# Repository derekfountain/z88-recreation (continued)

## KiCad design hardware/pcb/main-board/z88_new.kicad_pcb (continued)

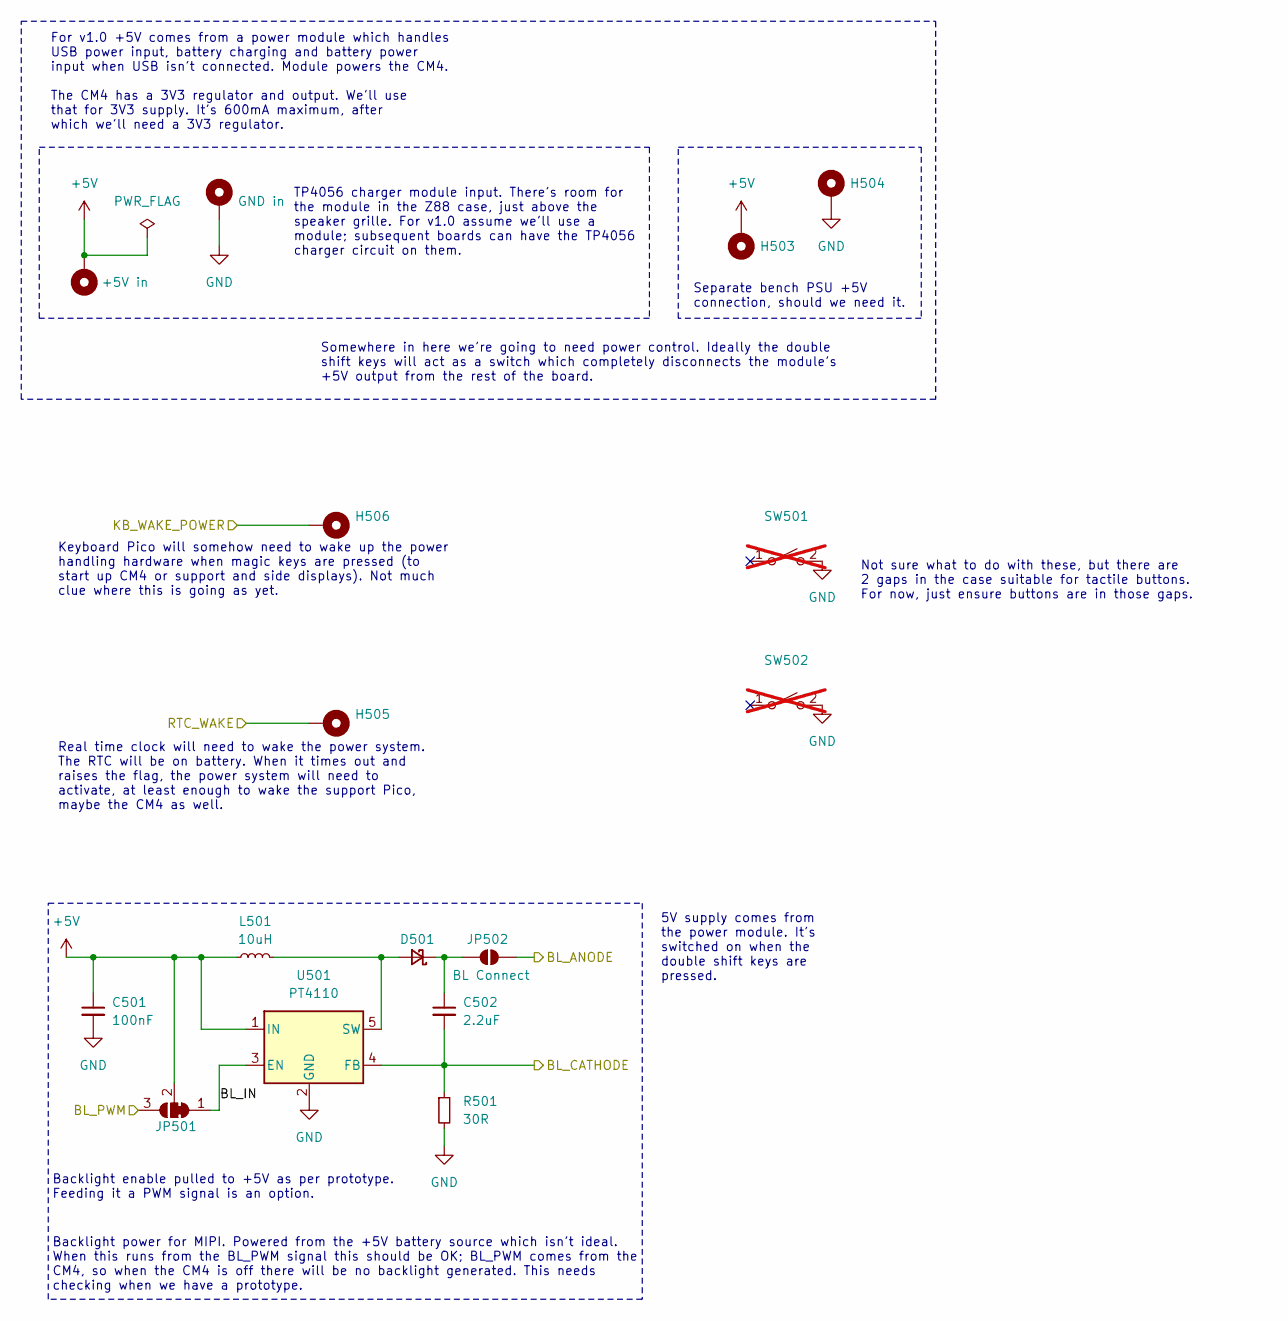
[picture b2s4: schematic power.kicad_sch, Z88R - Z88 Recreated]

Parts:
C501: 100nF; C_0805_2012Metric_Pad1.18x1.45mm_HandSolder
C502: 2.2uF; C_0805_2012Metric_Pad1.18x1.45mm_HandSolder
D501: D_Schottky_Small; D_1206_3216Metric_Pad1.42x1.75mm_HandSolder
H501: +5V in; MountingHole_2.2mm_M2_Pad
H502: GND in; MountingHole_2.2mm_M2_Pad
H503: +5V; MountingHole_2.2mm_M2_Pad
H504: GND; MountingHole_2.2mm_M2_Pad
H505: RTC Wake; TestPoint_THTPad_D2.0mm_Drill1.0mm
H506: KB Wake Power; TestPoint_THTPad_D2.0mm_Drill1.0mm
JP501: BL Source; SolderJumper-3_P1.3mm_Bridged2Bar12_Pad1.0x1.5mm
JP502: BL Connect; SolderJumper-2_P1.3mm_Open_Pad1.0x1.5mm
L501: 10uH; L_Coilcraft_XAL7070-XXX
R501: 30R; R_0805_2012Metric_Pad1.20x1.40mm_HandSolder
SW501, SW502: NO POP; SW_Tactile_SKHH_Angled; not fitted
U501: PT4110; SOT-89-5_Handsoldering

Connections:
+5V: C501.1, H501.1, H503.1, JP501.2 (C), L501.1, U501.1 (IN); also elsewhere on the board
/CM4_GPIO/BL_PWM: JP501.3 (B); also elsewhere on the board
/CM4_HighSpeed/BL_ANODE: JP502.2 (B); also elsewhere on the board
/CM4_HighSpeed/BL_CATHODE: C502.2, R501.1, U501.4 (FB); also elsewhere on the board
/Keyboard/KB_WAKE_POWER: H506.1; also elsewhere on the board
/Power/BL_IN: JP501.1 (A), U501.3 (EN)
/Power/RTC_WAKE: H505.1; also elsewhere on the board
GND: C501.2, H502.1, H504.1, R501.2, SW501.2 (B), SW502.2 (B), U501.2 (GND); also elsewhere on the board
unnamed: D501.2 (A), L501.2, U501.5 (SW)
unnamed: C502.1, D501.1 (K), JP502.1 (A)

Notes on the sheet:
Somewhere in here we're going to need power control. Ideally the double shift keys will act as a switch which completely disconnects the module's +5V output from the rest of the board.
For v1.0 +5V comes from a power module which handles USB power input, battery charging and battery power input when USB isn't connected. Module powers the CM4. The CM4 has a 3V3 regulator and output. We'll use that for 3V3 supply. It's 600mA maximum, after which we'll need a 3V3 regulator.
TP4056 charger module input. There's room for the module in the Z88 case, just above the speaker grille. For v1.0 assume we'll use a module; subsequent boards can have the TP4056 charger circuit on them.
Backlight power for MIPI. Powered from the +5V battery source which isn't ideal. When this runs from the BL_PWM signal this should be OK; BL_PWM comes from the CM4, so when the CM4 is off there will be no backlight generated. This needs checking when we have a prototype.
Real time clock will need to wake the power system. The RTC will be on battery. When it times out and raises the flag, the power system will need to activate, at least enough to wake the support Pico, maybe the CM4 as well.
Keyboard Pico will somehow need to wake up the power handling hardware when magic keys are pressed (to start up CM4 or support and side displays). Not much clue where this is going as yet.
Separate bench PSU +5V connection, should we need it.
Backlight enable pulled to +5V as per prototype. Feeding it a PWM signal is an option.
Not sure what to do with these, but there are 2 gaps in the case suitable for tactile buttons. For now, just ensure buttons are in those gaps.
5V supply comes from the power module. It's switched on when the double shift keys are pressed.

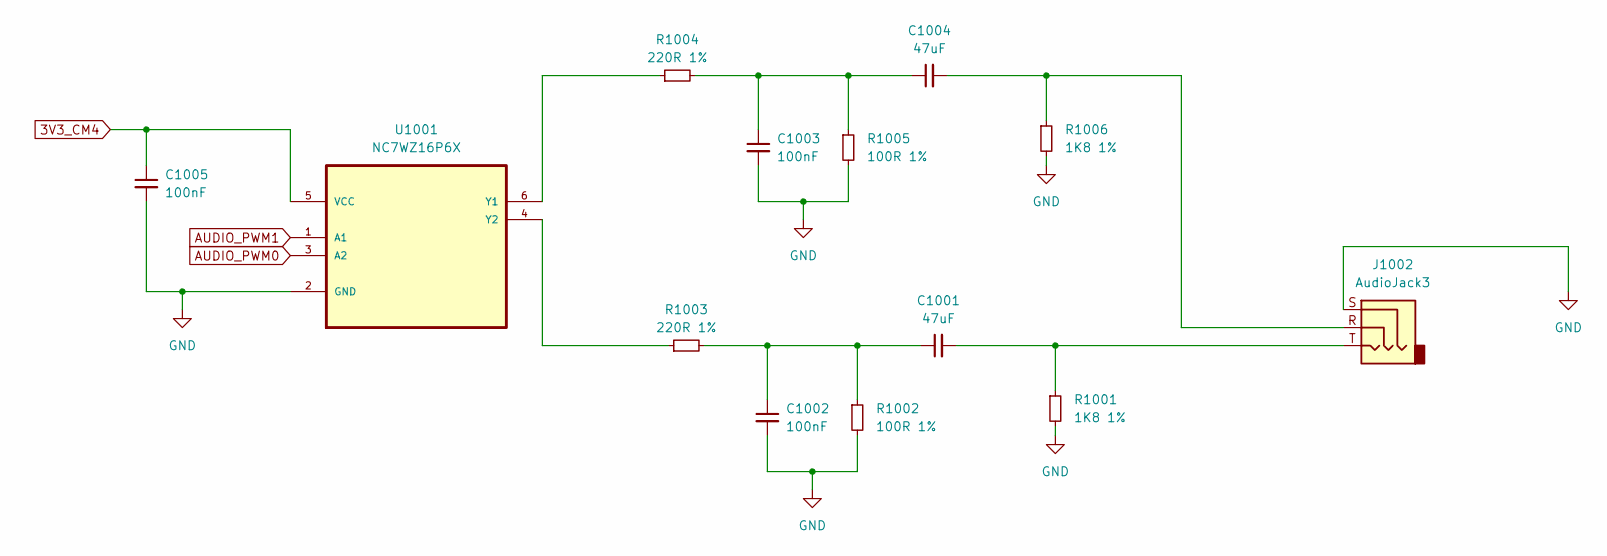
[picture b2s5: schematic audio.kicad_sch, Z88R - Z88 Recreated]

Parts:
C1001, C1004: 47uF; C_0805_2012Metric_Pad1.18x1.45mm_HandSolder
C1002, C1003, C1005: 100nF; C_0805_2012Metric_Pad1.18x1.45mm_HandSolder
J1002: AudioJack3; Jack_3.5mm_CUI_SJ1-3533NG_Horizontal
R1001, R1006: 1K8 1%; R_0805_2012Metric_Pad1.20x1.40mm_HandSolder
R1002, R1005: 100R 1%; R_0805_2012Metric_Pad1.20x1.40mm_HandSolder
R1003, R1004: 220R 1%; R_0805_2012Metric_Pad1.20x1.40mm_HandSolder
U1001: NC7WZ16P6X; SOT-363_SC-70-6_Handsoldering; MPN NC7WZ16P6X

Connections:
3V3_CM4: C1005.1, U1001.5 (VCC); also elsewhere on the board
AUDIO_PWM0: U1001.3 (A2); also elsewhere on the board
AUDIO_PWM1: U1001.1 (A1); also elsewhere on the board
GND: C1002.2, C1003.2, C1005.2, J1002.S, R1001.2, R1002.2, R1005.2, R1006.2, U1001.2 (GND); also elsewhere on the board
unnamed: C1001.1, C1002.1, R1002.1, R1003.2
unnamed: C1001.2, J1002.T, R1001.1
unnamed: C1003.1, C1004.1, R1004.2, R1005.1
unnamed: C1004.2, J1002.R, R1006.1
unnamed: R1004.1, U1001.6 (Y1)
unnamed: R1003.1, U1001.4 (Y2)

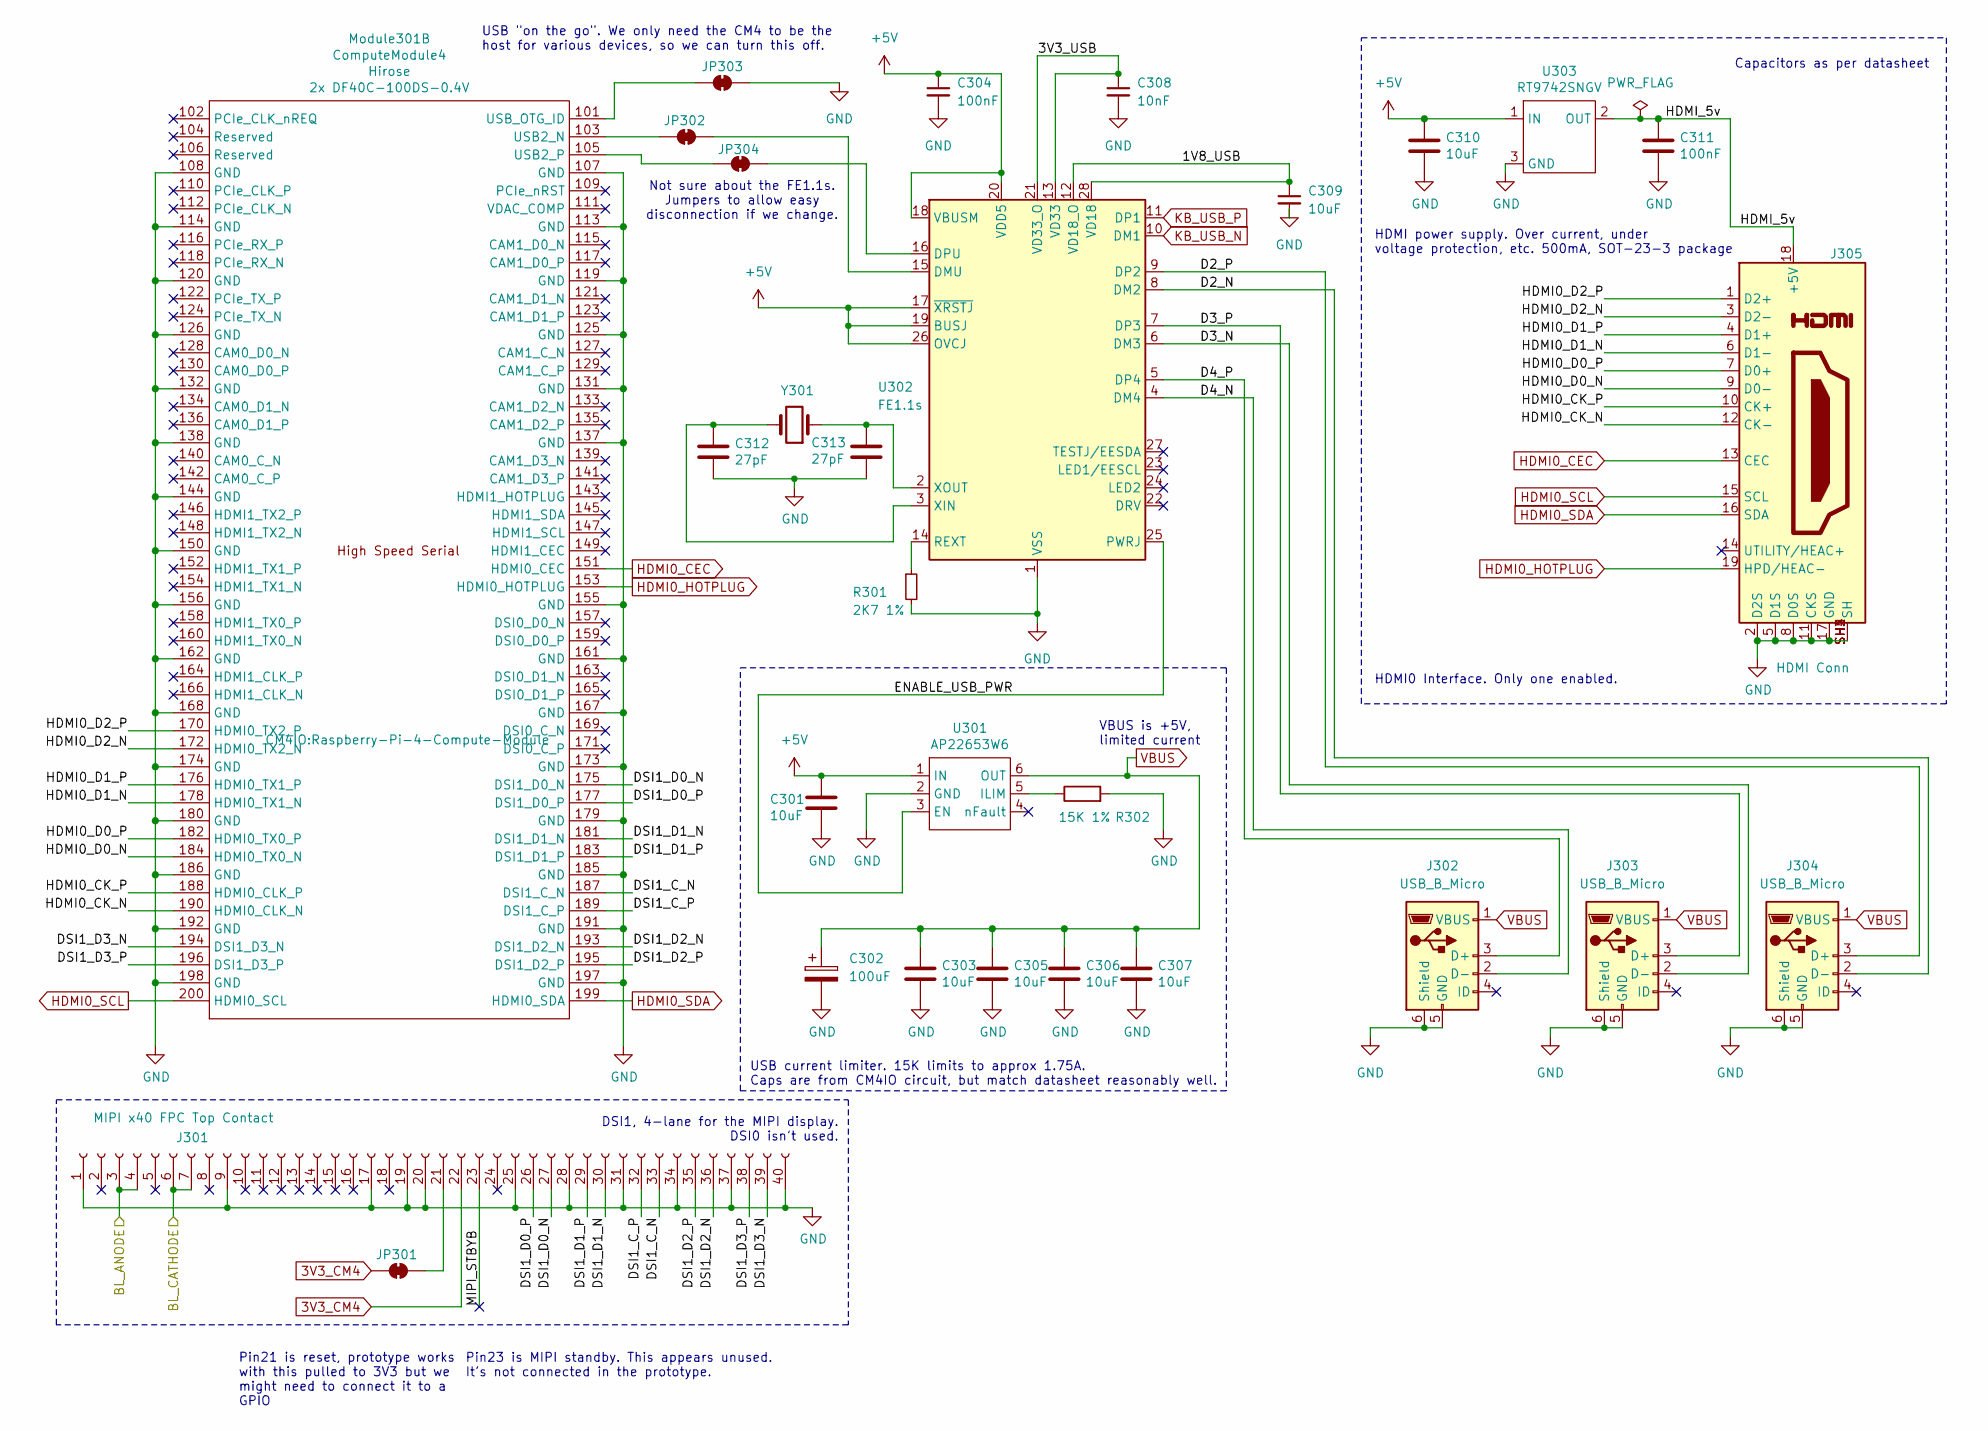
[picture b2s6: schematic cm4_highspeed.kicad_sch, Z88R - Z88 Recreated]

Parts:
C301, C303, C305, C306, C307: 10uF; C_0805_2012Metric_Pad1.18x1.45mm_HandSolder; Part Description 10uF 10% 10V Ceramic Capacitor X7R 0805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
C302: 100uF; C_0805_2012Metric_Pad1.18x1.45mm_HandSolder
C304: 100nF; C_0805_2012Metric_Pad1.18x1.45mm_HandSolder
C308: 10nF; C_0805_2012Metric_Pad1.18x1.45mm_HandSolder
C309: 10uF; C_0805_2012Metric_Pad1.18x1.45mm_HandSolder
C310: 10uF; C_0805_2012Metric_Pad1.18x1.45mm_HandSolder; Part Description 0.1uF 10% 16V Ceramic Capacitor X7R 040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
C311: 100nF; C_0805_2012Metric_Pad1.18x1.45mm_HandSolder; Part Description 0.1uF 10% 16V Ceramic Capacitor X7R 040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
C312, C313: 27pF; C_0805_2012Metric_Pad1.18x1.45mm_HandSolder; Part Description 27pF 5% 50V Ceramic Capacitor C0G, NP0 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
J301: MIPI x40 FPC Top Contact; Hirose_FH12-40S-0.5SH_1x40-1MP_P0.50mm_Horizontal
J302, J303, J304: USB_B_Micro; USB_Micro-B_Amphenol_10103594-0001LF_Horizontal
J305: HDMI Conn; EDAC 690-019-298-412; Part Description HDMI Connector, Right Angle, 19 Contact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
JP301: MIPI Reset; SolderJumper-2_P1.3mm_Bridged_Pad1.0x1.5mm
JP302, JP303, JP304: SolderJumper_2_Bridged; SolderJumper-2_P1.3mm_Bridged_Pad1.0x1.5mm
Module301: ComputeModule4; Raspberry-Pi-4-Compute-Module; Part Description 100 Position Connector Receptacle, Cent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
R301: 2K7 1%; R_0805_2012Metric_Pad1.20x1.40mm_HandSolder
R302: 15K 1%; R_0805_2012Metric_Pad1.20x1.40mm_HandSolder; Part Description Resistor 15K M1005 1% 63mW
U301: AP22653W6; SOT-23-6; Part Description Power Switch/Driver 1:1 P-Channel 2.1A 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
U302: FE1.1s; SSOP-28_3.9x9.9mm_P0.635mm
U303: RT9742SNGV; SOT-23; Part Description Power Switch/Driver 1:1 N-Channel 500mA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
Y301: ABLS-12.000MHZ-B4-T; Crystal_SMD_HC49-SD

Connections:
3V3_CM4: J301.22, JP301.1 (A); also elsewhere on the board
+5V: C301.1, C304.1, C310.1, U301.1 (IN), U302.17 (~XRSTJ), U302.18 (VBUSM), U302.19 (BUSJ), U302.20 (VDD5), U302.26 (OVCJ), U303.1 (IN); also elsewhere on the board
/CM4_HighSpeed/1V8_USB: C309.1, U302.12 (VD18_O), U302.28 (VD18)
/CM4_HighSpeed/3V3_USB: C308.1, U302.13 (VD33), U302.21 (VD33_O)
/CM4_HighSpeed/BL_ANODE: J301.3, J301.4; also elsewhere on the board
/CM4_HighSpeed/BL_CATHODE: J301.6, J301.7; also elsewhere on the board
/CM4_HighSpeed/D2_N: J304.2 (D-), U302.8 (DM2)
/CM4_HighSpeed/D2_P: J304.3 (D+), U302.9 (DP2)
/CM4_HighSpeed/D3_N: J303.2 (D-), U302.6 (DM3)
/CM4_HighSpeed/D3_P: J303.3 (D+), U302.7 (DP3)
/CM4_HighSpeed/D4_N: J302.2 (D-), U302.4 (DM4)
/CM4_HighSpeed/D4_P: J302.3 (D+), U302.5 (DP4)
/CM4_HighSpeed/DSI1_C_N: J301.33, Module301.187 (DSI1_C_N)
/CM4_HighSpeed/DSI1_C_P: J301.32, Module301.189 (DSI1_C_P)
/CM4_HighSpeed/DSI1_D0_N: J301.27, Module301.175 (DSI1_D0_N)
/CM4_HighSpeed/DSI1_D0_P: J301.26, Module301.177 (DSI1_D0_P)
/CM4_HighSpeed/DSI1_D1_N: J301.30, Module301.181 (DSI1_D1_N)
/CM4_HighSpeed/DSI1_D1_P: J301.29, Module301.183 (DSI1_D1_P)
/CM4_HighSpeed/DSI1_D2_N: J301.36, Module301.193 (DSI1_D2_N)
/CM4_HighSpeed/DSI1_D2_P: J301.35, Module301.195 (DSI1_D2_P)
/CM4_HighSpeed/DSI1_D3_N: J301.39, Module301.194 (DSI1_D3_N)
/CM4_HighSpeed/DSI1_D3_P: J301.38, Module301.196 (DSI1_D3_P)
/CM4_HighSpeed/ENABLE_USB_PWR: U301.3 (EN), U302.25 (PWRJ)
/CM4_HighSpeed/HDMI0_CK_N: J305.12 (CK-), Module301.190 (HDMI0_CLK_N)
/CM4_HighSpeed/HDMI0_CK_P: J305.10 (CK+), Module301.188 (HDMI0_CLK_P)
/CM4_HighSpeed/HDMI0_D0_N: J305.9 (D0-), Module301.184 (HDMI0_TX0_N)
/CM4_HighSpeed/HDMI0_D0_P: J305.7 (D0+), Module301.182 (HDMI0_TX0_P)
/CM4_HighSpeed/HDMI0_D1_N: J305.6 (D1-), Module301.178 (HDMI0_TX1_N)
/CM4_HighSpeed/HDMI0_D1_P: J305.4 (D1+), Module301.176 (HDMI0_TX1_P)
/CM4_HighSpeed/HDMI0_D2_N: J305.3 (D2-), Module301.172 (HDMI0_TX2_N)
/CM4_HighSpeed/HDMI0_D2_P: J305.1 (D2+), Module301.170 (HDMI0_TX2_P)
/CM4_HighSpeed/HDMI_5v: C311.1, J305.18 (+5V), U303.2 (OUT)
/CM4_HighSpeed/MIPI_STBYB: J301.23
GND: C301.2, C302.2, C303.2, C304.2, C305.2, C306.2, C307.2, C308.2, C309.2, C310.2, C311.2, C312.2, C313.2, J301.1, J301.9, J301.17, J301.19, J301.20, J301.25, J301.28, J301.31, J301.34, J301.37, J301.40, J302.5 (GND), J302.6 (Shield), J303.5 (GND), J303.6 (Shield), J304.5 (GND), J304.6 (Shield), J305.2 (D2S), J305.5 (D1S), J305.8 (D0S), J305.11 (CKS), J305.17 (GND), J305.SH1 (SH), J305.SH2 (SH), J305.SH3 (SH), J305.SH4 (SH), JP303.2 (B), Module301.107 (GND), Module301.108 (GND), Module301.113 (GND), Module301.114 (GND), Module301.119 (GND), Module301.120 (GND), Module301.125 (GND), Module301.126 (GND), Module301.131 (GND), Module301.132 (GND), Module301.137 (GND), Module301.138 (GND), Module301.144 (GND), Module301.150 (GND), Module301.155 (GND), Module301.156 (GND), Module301.161 (GND), Module301.162 (GND), Module301.167 (GND), Module301.168 (GND), Module301.173 (GND), Module301.174 (GND), Module301.179 (GND), Module301.180 (GND), Module301.185 (GND), Module301.186 (GND), Module301.191 (GND), Module301.192 (GND), Module301.197 (GND), Module301.198 (GND), R301.2, R302.2, U301.2 (GND), U302.1 (VSS), U303.3 (GND); also elsewhere on the board
HDMI0_CEC: J305.13 (CEC), Module301.151 (HDMI0_CEC)
HDMI0_HOTPLUG: J305.19 (HPD/HEAC-), Module301.153 (HDMI0_HOTPLUG)
HDMI0_SCL: J305.15 (SCL), Module301.200 (HDMI0_SCL)
HDMI0_SDA: J305.16 (SDA), Module301.199 (HDMI0_SDA)
KB_USB_N: U302.10 (DM1); also elsewhere on the board
KB_USB_P: U302.11 (DP1); also elsewhere on the board
unnamed: J301.21, JP301.2 (B)
unnamed: JP302.1 (A), Module301.103 (USB2_N)
unnamed: JP302.2 (B), U302.15 (DMU)
unnamed: JP303.1 (A), Module301.101 (USB_OTG_ID)
unnamed: JP304.1 (A), Module301.105 (USB2_P)
unnamed: JP304.2 (B), U302.16 (DPU)
unnamed: R302.1, U301.5 (ILIM)
unnamed: R301.1, U302.14 (REXT)
unnamed: C312.1, U302.3 (XIN), Y301.2
unnamed: C313.1, U302.2 (XOUT), Y301.1
VBUS: C302.1, C303.1, C305.1, C306.1, C307.1, J302.1 (VBUS), J303.1 (VBUS), J304.1 (VBUS), U301.6 (OUT)

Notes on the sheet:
DSI1, 4-lane for the MIPI display. DSI0 isn't used.
Pin23 is MIPI standby. This appears unused. It's not connected in the prototype.
USB "on the go". We only need the CM4 to be the host for various devices, so we can turn this off.
VBUS is +5V, limited current
Not sure about the FE1.1s. Jumpers to allow easy disconnection if we change.
Pin21 is reset, prototype works with this pulled to 3V3 but we might need to connect it to a GPIO
USB current limiter. 15K limits to approx 1.75A. Caps are from CM4IO circuit, but match datasheet reasonably well.
Capacitors as per datasheet
HDMI power supply. Over current, under voltage protection, etc. 500mA, SOT-23-3 package
HDMI0 Interface. Only one enabled.

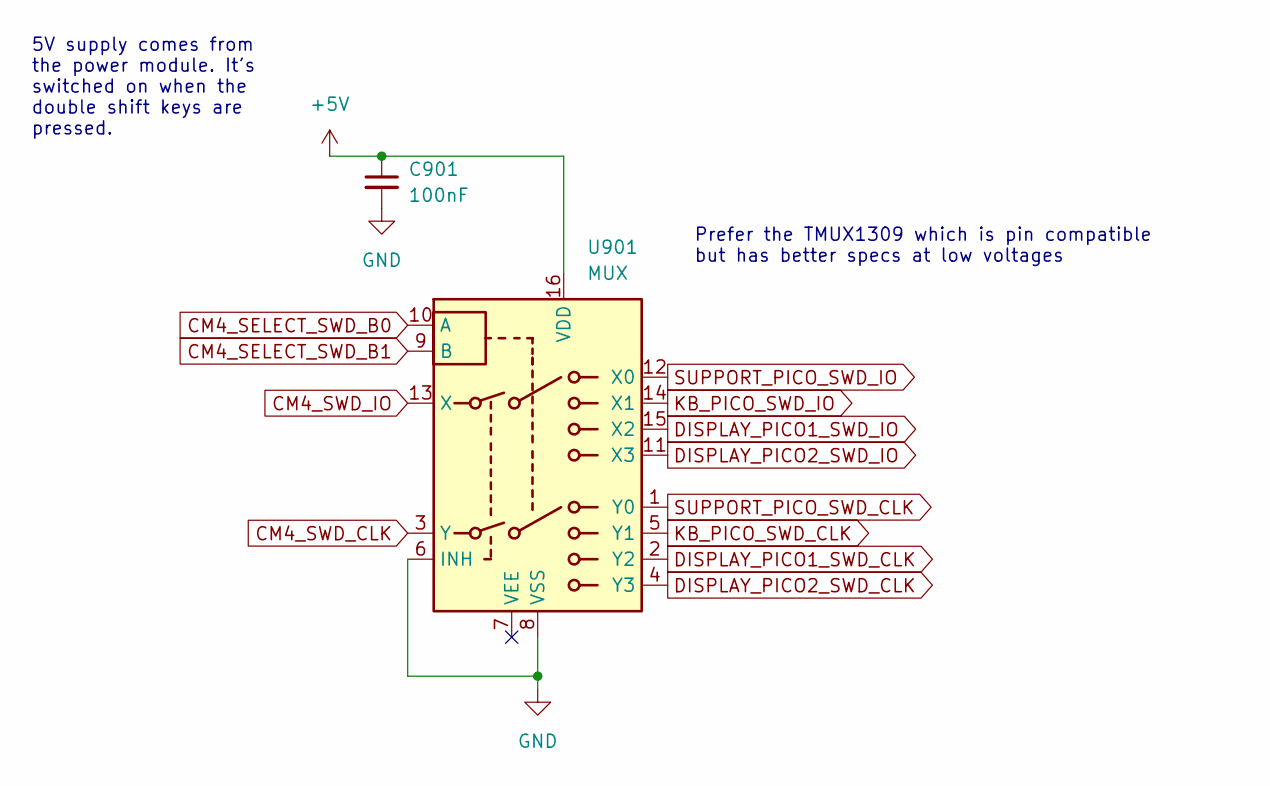
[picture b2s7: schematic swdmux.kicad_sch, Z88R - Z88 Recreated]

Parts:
C901: 100nF; C_0805_2012Metric_Pad1.18x1.45mm_HandSolder
U901: MUX; Texas_DYY0016A_TSOT-23-16_4.2x2.0mm_P0.5mm

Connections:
+5V: C901.1, U901.16 (VDD); also elsewhere on the board
CM4_SELECT_SWD_B0: U901.10 (A); also elsewhere on the board
CM4_SELECT_SWD_B1: U901.9 (B); also elsewhere on the board
CM4_SWD_CLK: U901.3 (Y); also elsewhere on the board
CM4_SWD_IO: U901.13 (X); also elsewhere on the board
DISPLAY_PICO1_SWD_CLK: U901.2 (Y2); also elsewhere on the board
DISPLAY_PICO1_SWD_IO: U901.15 (X2); also elsewhere on the board
DISPLAY_PICO2_SWD_CLK: U901.4 (Y3); also elsewhere on the board
DISPLAY_PICO2_SWD_IO: U901.11 (X3); also elsewhere on the board
GND: C901.2, U901.6 (INH), U901.8 (VSS); also elsewhere on the board
KB_PICO_SWD_CLK: U901.5 (Y1); also elsewhere on the board
KB_PICO_SWD_IO: U901.14 (X1); also elsewhere on the board
SUPPORT_PICO_SWD_CLK: U901.1 (Y0); also elsewhere on the board
SUPPORT_PICO_SWD_IO: U901.12 (X0); also elsewhere on the board

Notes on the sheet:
Prefer the TMUX1309 which is pin compatible but has better specs at low voltages
5V supply comes from the power module. It's switched on when the double shift keys are pressed.

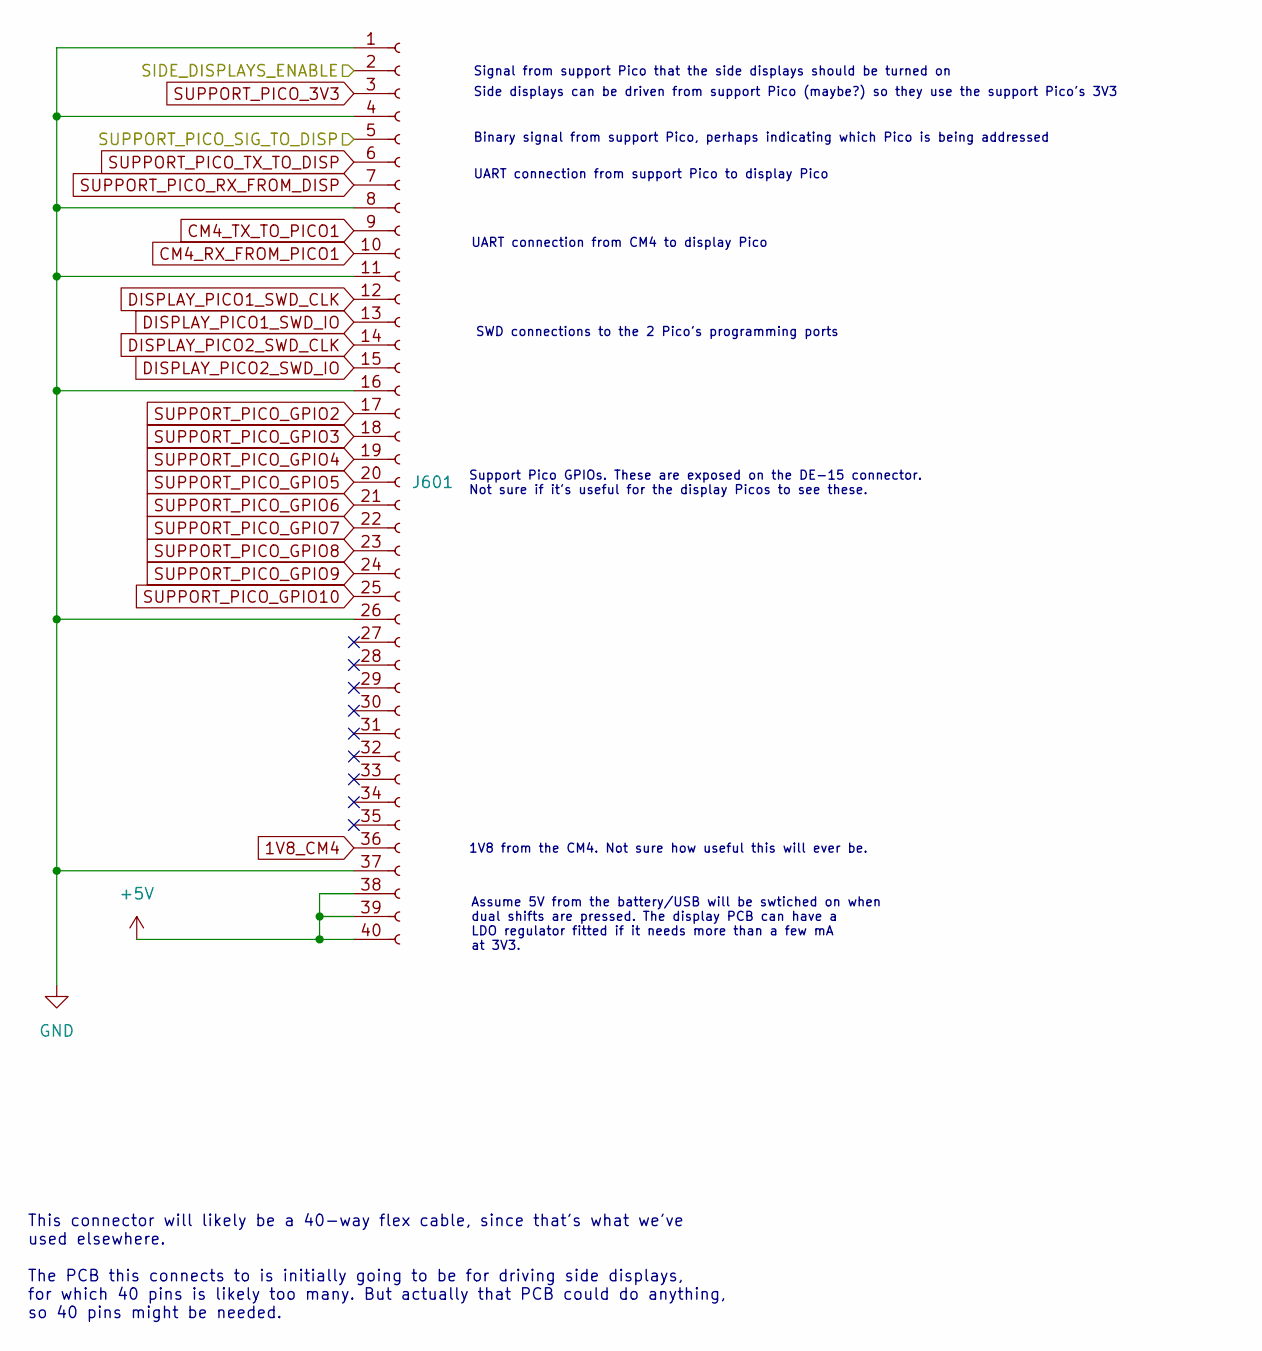
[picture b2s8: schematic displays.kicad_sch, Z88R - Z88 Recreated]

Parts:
J601: DISP_PCB x40 FPC; Hirose_FH12-40S-0.5SH_1x40-1MP_P0.50mm_Horizontal

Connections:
1V8_CM4: J601.36; also elsewhere on the board
+5V: J601.38, J601.39, J601.40; also elsewhere on the board
/Side Displays/SIDE_DISPLAYS_ENABLE: J601.2; also elsewhere on the board
/Side Displays/SUPPORT_PICO_SIG_TO_DISP: J601.5; also elsewhere on the board
CM4_RX_FROM_PICO1: J601.10; also elsewhere on the board
CM4_TX_TO_PICO1: J601.9; also elsewhere on the board
DISPLAY_PICO1_SWD_CLK: J601.12; also elsewhere on the board
DISPLAY_PICO1_SWD_IO: J601.13; also elsewhere on the board
DISPLAY_PICO2_SWD_CLK: J601.14; also elsewhere on the board
DISPLAY_PICO2_SWD_IO: J601.15; also elsewhere on the board
GND: J601.1, J601.4, J601.8, J601.11, J601.16, J601.26, J601.37; also elsewhere on the board
SUPPORT_PICO_3V3: J601.3; also elsewhere on the board
SUPPORT_PICO_GPIO2: J601.17; also elsewhere on the board
SUPPORT_PICO_GPIO3: J601.18; also elsewhere on the board
SUPPORT_PICO_GPIO4: J601.19; also elsewhere on the board
SUPPORT_PICO_GPIO5: J601.20; also elsewhere on the board
SUPPORT_PICO_GPIO6: J601.21; also elsewhere on the board
SUPPORT_PICO_GPIO7: J601.22; also elsewhere on the board
SUPPORT_PICO_GPIO8: J601.23; also elsewhere on the board
SUPPORT_PICO_GPIO9: J601.24; also elsewhere on the board
SUPPORT_PICO_GPIO10: J601.25; also elsewhere on the board
SUPPORT_PICO_RX_FROM_DISP: J601.7; also elsewhere on the board
SUPPORT_PICO_TX_TO_DISP: J601.6; also elsewhere on the board

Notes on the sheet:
Signal from support Pico that the side displays should be turned on
1V8 from the CM4. Not sure how useful this will ever be.
Assume 5V from the battery/USB will be swtiched on when dual shifts are pressed. The display PCB can have a LDO regulator fitted if it needs more than a few mA at 3V3.
SWD connections to the 2 Pico's programming ports
UART connection from support Pico to display Pico
Support Pico GPIOs. These are exposed on the DE-15 connector. Not sure if it's useful for the display Picos to see these.
This connector will likely be a 40-way flex cable, since that's what we've used elsewhere. The PCB this connects to is initially going to be for driving side displays, for which 40 pins is likely too many. But actually that PCB could do anything, so 40 pins might be needed.
Binary signal from support Pico, perhaps indicating which Pico is being addressed
UART connection from CM4 to display Pico
Side displays can be driven from support Pico (maybe?) so they use the support Pico's 3V3

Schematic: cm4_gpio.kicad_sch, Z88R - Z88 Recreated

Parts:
C401: 10uF; C_0805_2012Metric_Pad1.18x1.45mm_HandSolder; Part Description 10uF 10% 10V Ceramic Capacitor X7R 0805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
C402: 10uF; C_0805_2012Metric_Pad1.18x1.45mm_HandSolder
J401: PinHeader_2x20_P2.00mm_Vertical_SMD; Part Description PinHeader_2x20_P2.54mm_Vertical
J402: CM4Lite SD Card; Conn_uSDcard
Module301: ComputeModule4; Raspberry-Pi-4-Compute-Module; Part Description 100 Position Connector Receptacle, Cent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
TP401: SD Pwr On; TestPoint_THTPad_D2.0mm_Drill1.0mm
TP402: CM4 I2C Clk; TestPoint_THTPad_D2.0mm_Drill1.0mm
TP403: CM4 I2C Da; TestPoint_THTPad_D2.0mm_Drill1.0mm
TP404: SD CLK; TestPoint_THTPad_D2.0mm_Drill1.0mm
TP406: SD Vdd Ov; TestPoint_THTPad_D2.0mm_Drill1.0mm
TP408: Tx Disp Pico; TestPoint_THTPad_D2.0mm_Drill1.0mm
TP409: Rx Disp Pico; TestPoint_THTPad_D2.0mm_Drill1.0mm
TP410: GPIO19; TestPoint_THTPad_D2.0mm_Drill1.0mm
U402: RT9742SNGV; SOT-23; Part Description Power Switch/Driver 1:1 N-Channel 500mA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

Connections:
1V8_CM4: Module301.88 (+1.8v_(Output)), Module301.90 (+1.8v_(Output)); also elsewhere on the board
3V3_CM4: C402.1, J401.1, J401.17, Module301.78 (GPIO_VREF(1.8v/3.3v_Input)), Module301.84 (+3.3v_(Output)), Module301.86 (+3.3v_(Output)), U402.1 (IN); also elsewhere on the board
+5V: J401.2, J401.4, Module301.77 (+5v_(Input)), Module301.79 (+5v_(Input)), Module301.81 (+5v_(Input)), Module301.83 (+5v_(Input)), Module301.85 (+5v_(Input)), Module301.87 (+5v_(Input)); also elsewhere on the board
/CM4_GPIO/BL_PWM: J401.12, Module301.49 (GPIO18); also elsewhere on the board
/CM4_GPIO/GLOBAL_ENABLE: Module301.99 (Global_EN); also elsewhere on the board
AUDIO_PWM0: J401.32, Module301.31 (GPIO12); also elsewhere on the board
AUDIO_PWM1: J401.33, Module301.28 (GPIO13); also elsewhere on the board
CM4_GPIO2: J401.3, Module301.58 (GPIO2)
CM4_GPIO3: J401.5, Module301.56 (GPIO3)
CM4_GPIO6: J401.31, Module301.30 (GPIO6)
CM4_GPIO9: J401.21, Module301.40 (GPIO9)
CM4_GPIO10: J401.19, Module301.44 (GPIO10)
CM4_GPIO11: J401.23, Module301.38 (GPIO11)
CM4_GPIO16: J401.36, Module301.29 (GPIO16)
CM4_GPIO17: J401.11, Module301.50 (GPIO17)
CM4_GPIO19: J401.35, Module301.26 (GPIO19), TP410.1
CM4_GPIO20: J401.38, Module301.27 (GPIO20)
CM4_GPIO21: J401.40, Module301.25 (GPIO21)
CM4_GPIO22: J401.15, Module301.46 (GPIO22)
CM4_GPIO25: J401.22, Module301.41 (GPIO25)
CM4_GPIO26: J401.37, Module301.24 (GPIO26)
CM4_GPIO27: J401.13, Module301.48 (GPIO27)
CM4_I2C_CLK: J401.28, Module301.35 (ID_SC); also elsewhere on the board
CM4_I2C_DAT: J401.27, Module301.36 (ID_SD); also elsewhere on the board
CM4_RX_FROM_PICO1: J401.29, Module301.34 (GPIO5), TP409.1; also elsewhere on the board
CM4_SELECT_SWD_B0: J401.16, Module301.47 (GPIO23); also elsewhere on the board
CM4_SELECT_SWD_B1: J401.18, Module301.45 (GPIO24); also elsewhere on the board
CM4_SWD_CLK: J401.24, Module301.39 (GPIO8); also elsewhere on the board
CM4_SWD_IO: J401.26, Module301.37 (GPIO7); also elsewhere on the board
CM4_TX_TO_PICO1: J401.7, Module301.54 (GPIO4), TP408.1; also elsewhere on the board
GND: C401.2, C402.2, J401.6, J401.9, J401.14, J401.20, J401.25, J401.30, J401.34, J401.39, J402.6 (VSS), J402.9 (SHIELD), Module301.1 (GND), Module301.2 (GND), Module301.7 (GND), Module301.8 (GND), Module301.13 (GND), Module301.14 (GND), Module301.22 (GND), Module301.23 (GND), Module301.32 (GND), Module301.33 (GND), Module301.42 (GND), Module301.43 (GND), Module301.52 (GND), Module301.53 (GND), Module301.59 (GND), Module301.60 (GND), Module301.65 (GND), Module301.66 (GND), Module301.71 (GND), Module301.74 (GND), Module301.97 (Camera_GPIO), Module301.98 (GND), U402.3 (GND); also elsewhere on the board
unnamed: C401.1, J402.4 (VDD), U402.2 (OUT)
unnamed: Module301.80 (SCL0), TP402.1
unnamed: Module301.82 (SDA0), TP403.1
unnamed: Module301.75 (SD_PWR_ON), TP401.1
unnamed: Module301.73 (SD_VDD_Override), TP406.1
RX_FROM_SUPPORT_PICO: J401.10, Module301.51 (GPIO15); also elsewhere on the board
SD_CLK: J402.5 (CLK), Module301.57 (SD_CLK), TP404.1
SD_CMD: J402.3 (CMD), Module301.62 (SD_CMD)
SD_DAT0: J402.7 (DAT0), Module301.63 (SD_DAT0)
SD_DAT1: J402.8 (DAT1), Module301.67 (SD_DAT1)
SD_DAT2: J402.1 (DAT2), Module301.69 (SD_DAT2)
SD_DAT3: J402.2 (DAT3/CD), Module301.61 (SD_DAT3)
TX_TO_SUPPORT_PICO: J401.8, Module301.55 (GPIO14); also elsewhere on the board

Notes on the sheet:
CM4 GPIOs use 3V3
High side power switch to drive the SD card reader. CM4 boots and runs from SD card, so power to SD card is permanently enabled.
CM4Lite SDCARD I/F
ID_SD is GPIO0 ID_SC is GPIO1
5V supply comes from the power module. It's switched on when the double shift keys are pressed.
40Way CM4 GPIO Header
We probably won't put header pins on this, but having the footprint on the board such that we can solder connections to the CM4 GPIOs will likely be useful

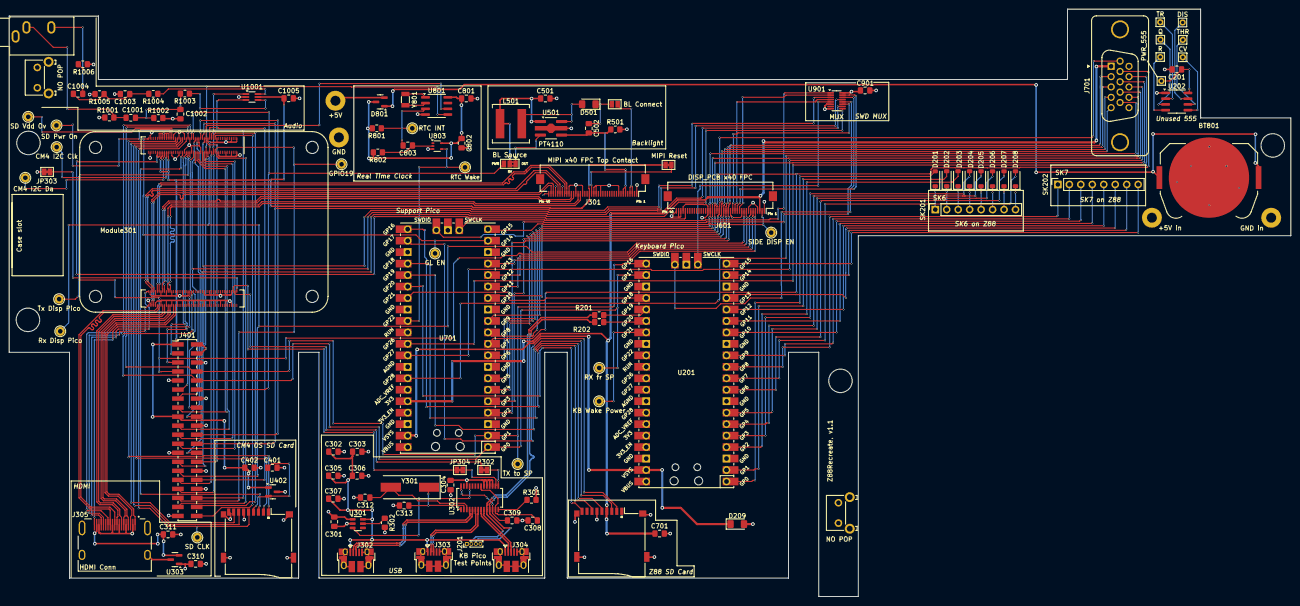
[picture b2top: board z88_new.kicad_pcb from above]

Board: 4 copper layers, 283.9 x 130.1 mm, 117 parts (0 on the bottom side), 173 nets.

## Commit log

2025-11-17 initial
2025-11-17 add keyboard prototype
2025-11-17 remove large video from prototype
2025-11-17 add some early helper scripts
2025-11-17 update images
2025-11-17 add early 3D print bits and pieces
2025-11-17 add assorted documentation
2025-11-17 add the support pico software directory with the uart test case
2025-11-17 update the pico_uart example
2025-11-17 add an uploader script for the support code ELF
2025-11-18 add support pico's SD card reader example
2025-11-18 add a RTC->Support Pico timer signal test
2025-11-21 add support pico to CM4 signal example
2025-11-21 add application board mountings 3d print
2025-12-02 add early version of application board
2025-12-04 start layout of application board
2025-12-04 more layout work
2025-12-06 layout complete, first draft, needs tidying
2025-12-06 fab1.0 off to JLC
2025-12-08 start v1.1, missed some tidyups and a label
2025-12-18 update block diagram with current thinking and power domains
2025-12-29 start next board iteration, add latch and pico power bits
2025-12-29 CM4 power switch
2025-12-30 add i2c connection to the support pico so it can control the RTC
2025-12-30 turn the KB diodes round, oops
2025-12-30 make a start on RP2040 to replace the KB pico
2025-12-30 more work on KB pico replacement
2025-12-31 more working out of the KB pico replacement
2026-01-01 start the support pico rp2040 replacement
2026-01-01 rename the pico bits to RP2040, still a few things to check
2026-01-01 a few more tidyups, almost ready for dual shifts stuff now
2026-01-01 more support rp2040 cleanups
2026-01-04 start v1.1 pcb, add FPC connector label
2026-01-08 add support pico utility to activate the application board
2026-01-09 add the ELF version of the keyboard software, this is required to reprogram the pico via SWD
2026-01-09 application board blink example
2026-01-27 increase height of application board mount by 1mm
2026-01-28 change activate app board to remove the blink
2026-01-28 start oled demo code
2026-01-28 sh1106 OLED code in the demo
2026-01-30 rename OLED demo to SSH1106 OLED demo
2026-01-30 start a SSD1306 app board example, not sure what chip my displays are using
2026-02-02 fix my SH1106 code, my screens have an offset
2026-02-04 add top bezel for the 1.3inch side screen
2026-02-04 add the 1.3inch oled lower bezel
2026-02-04 add a pause in the application board pico code for the i2c bus to get going
2026-02-12 update support pico links: UART0 to CM4, UART1 to app board Pico0, GPIOs to app board Pico1. KB pico outstanding
2026-02-12 disconnect the keyboard pico from the support pico, that link isn't required
2026-02-12 add note about support Pico to application board pico1
2026-02-12 rename display board things to application board things
2026-02-12 more renaming and tidying up of internal interfaces
2026-02-13 tidy the keyboard comms
2026-02-13 rename app board picos to 1 and 2, to match the application board schematics
2026-02-13 rename CM4 to support RP link
2026-02-13 move an SWD GPIO freeing up UART4 on the CM4. use that for talking to the appb Pico2
2026-02-13 oops, missed a couple of references to GPIOs i'd changed
2026-02-15 start the firmware for the support pico, for the v1.0 board
2026-02-16 start thinking about a status display on the left side OLED display
2026-03-18 establish a hello_world UART connection from main board to app board pico
2026-03-19 update strings sent from support to left pico, looks more sensible even if it's not
2026-03-19 add an application for Pico2 on the application board
